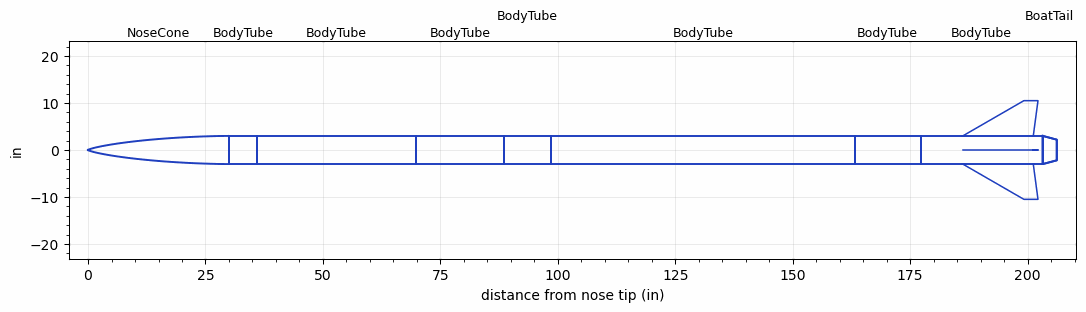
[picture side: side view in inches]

<RASAeroDocument>
 <FileVersion>2</FileVersion>
 <RocketDesign>
  <NoseCone>
   <Length>30</Length>
   <Diameter>6</Diameter>
   <Shape>LV-Haack</Shape>
   <Location>0</Location>
  </NoseCone>
  <BodyTube>
   <Length>6</Length>
   <Diameter>6</Diameter>
   <Location>30</Location>
  </BodyTube>
  <BodyTube>
   <Length>33.8</Length>
   <Diameter>6</Diameter>
   <Location>36</Location>
  </BodyTube>
  <BodyTube>
   <Length>18.7</Length>
   <Diameter>6</Diameter>
   <Location>69.8</Location>
  </BodyTube>
  <BodyTube>
   <Length>10</Length>
   <Diameter>6</Diameter>
   <Location>88.5</Location>
  </BodyTube>
  <BodyTube>
   <Length>64.69</Length>
   <Diameter>6</Diameter>
   <Location>98.5</Location>
  </BodyTube>
  <BodyTube>
   <Length>14</Length>
   <Diameter>6</Diameter>
   <Location>163.19</Location>
  </BodyTube>
  <BodyTube>
   <Length>26</Length>
   <Diameter>6</Diameter>
   <Location>177.19</Location>
   <BoattailLength>3</BoattailLength>
   <BoattailRearDiameter>4.4</BoattailRearDiameter>
   <Fin>
    <Count>4</Count>
    <Chord>15</Chord>
    <Span>7.5</Span>
    <SweepDistance>13</SweepDistance>
    <TipChord>3</TipChord>
    <Thickness>0.3</Thickness>
    <LERadius>0.01</LERadius>
    <Location>17</Location>
    <AirfoilSection>Hexagonal</AirfoilSection>
    <FX1>0.15</FX1>
    <FX3>0.15</FX3>
   </Fin>
  </BodyTube>
  <BoatTail>
   <Length>3</Length>
   <Diameter>6</Diameter>
   <RearDiameter>4.4</RearDiameter>
   <Location>203.19</Location>
  </BoatTail>
  <Surface>Camouflage Paint</Surface>
  <ModifiedBarrowman>True</ModifiedBarrowman>
  <Turbulence>True</Turbulence>
  <UseBooster1>False</UseBooster1>
  <UseBooster2>False</UseBooster2>
 </RocketDesign>
 <LaunchSite>
  <Altitude>2950</Altitude>
  <Pressure>27</Pressure>
  <RodAngle>8</RodAngle>
  <RodLength>32.8</RodLength>
  <Temperature>76</Temperature>
  <WindSpeed>18</WindSpeed>
 </LaunchSite>
 <Recovery>
  <Altitude1>1000</Altitude1>
  <Altitude2>1000</Altitude2>
  <DeviceType1>None</DeviceType1>
  <DeviceType2>None</DeviceType2>
  <Event1>False</Event1>
  <Event2>False</Event2>
  <Size1>1</Size1>
  <Size2>1</Size2>
  <EventType1>None</EventType1>
  <EventType2>None</EventType2>
  <CD1>1.33</CD1>
  <CD2>1.33</CD2>
 </Recovery>
 <SimulationList>
  <Simulation>
   <SustainerEngine>IGNIS  (TAMUSRT)</SustainerEngine>
   <SustainerLaunchWt>141.31</SustainerLaunchWt>
   <SustainerCG>129</SustainerCG>
   <SustainerIgnitionDelay>0</SustainerIgnitionDelay>
   <Booster1SeparationDelay>0</Booster1SeparationDelay>
   <Booster1IgnitionDelay>0</Booster1IgnitionDelay>
   <IncludeBooster1>False</IncludeBooster1>
   <Booster2Delay>0</Booster2Delay>
   <IncludeBooster2>False</IncludeBooster2>
   <TimetoApogee>39.09945</TimetoApogee>
   <MaxAltitude>21522.93</MaxAltitude>
   <MaxVelocity>1241.325</MaxVelocity>
  </Simulation>
  <Simulation>
   <SustainerEngine>COMB_PLUS  (TAMUSRT)</SustainerEngine>
   <SustainerLaunchWt>128</SustainerLaunchWt>
   <SustainerCG>125</SustainerCG>
   <SustainerIgnitionDelay>0</SustainerIgnitionDelay>
   <Booster1SeparationDelay>0</Booster1SeparationDelay>
   <Booster1IgnitionDelay>0</Booster1IgnitionDelay>
   <IncludeBooster1>False</IncludeBooster1>
   <Booster2Delay>0</Booster2Delay>
   <IncludeBooster2>False</IncludeBooster2>
   <TimetoApogee>47.78799</TimetoApogee>
   <MaxAltitude>35467.81</MaxAltitude>
   <MaxVelocity>1758.893</MaxVelocity>
  </Simulation>
  <Simulation>
   <SustainerEngine>COMBINED_30  (TAMUSRT)</SustainerEngine>
   <SustainerLaunchWt>149</SustainerLaunchWt>
   <SustainerCG>130</SustainerCG>
   <SustainerIgnitionDelay>0</SustainerIgnitionDelay>
   <Booster1SeparationDelay>0</Booster1SeparationDelay>
   <Booster1IgnitionDelay>0</Booster1IgnitionDelay>
   <IncludeBooster1>False</IncludeBooster1>
   <Booster2Delay>0</Booster2Delay>
   <IncludeBooster2>False</IncludeBooster2>
   <TimetoApogee>45.99829</TimetoApogee>
   <MaxAltitude>31779.34</MaxAltitude>
   <MaxVelocity>1582.848</MaxVelocity>
  </Simulation>
  <Simulation>
   <SustainerEngine>CUST  (TAMUSRT)</SustainerEngine>
   <SustainerLaunchWt>152</SustainerLaunchWt>
   <SustainerCG>132</SustainerCG>
   <SustainerIgnitionDelay>0</SustainerIgnitionDelay>
   <Booster1SeparationDelay>0</Booster1SeparationDelay>
   <Booster1IgnitionDelay>0</Booster1IgnitionDelay>
   <IncludeBooster1>False</IncludeBooster1>
   <Booster2Delay>0</Booster2Delay>
   <IncludeBooster2>False</IncludeBooster2>
  </Simulation>
  <Simulation>
   <SustainerEngine>TRIAL  (TAMUSRT)</SustainerEngine>
   <SustainerLaunchWt>143</SustainerLaunchWt>
   <SustainerNozzleDiameter>3.5</SustainerNozzleDiameter>
   <SustainerCG>131</SustainerCG>
   <SustainerIgnitionDelay>0</SustainerIgnitionDelay>
   <Booster1SeparationDelay>0</Booster1SeparationDelay>
   <Booster1IgnitionDelay>0</Booster1IgnitionDelay>
   <IncludeBooster1>False</IncludeBooster1>
   <Booster2Delay>0</Booster2Delay>
   <IncludeBooster2>False</IncludeBooster2>
   <TimetoApogee>41.71901</TimetoApogee>
   <MaxAltitude>26628.62</MaxAltitude>
   <MaxVelocity>1520.361</MaxVelocity>
  </Simulation>
 </SimulationList>
</RASAeroDocument>
